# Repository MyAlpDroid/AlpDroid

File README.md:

<H1> Il existe désormais une version commerciale de la solution proposée et installée par les meilleurs préparateurs du marché </H1>

[Français](https://github.com/MyAlpDroid/AlpDroid/blob/main/README.md)    [English](https://github.com/MyAlpDroid/AlpDroid/blob/main/README.en.md)

Alpine : MyAlpdroid Video Demo 

<H1> Alpine : Remplacer le poste multimédia  par un poste Android </H1>

Le poste multimédia Alpine présente 2 inconvénients : il n'est pas compatible Android Auto/Apple CarPlay. Il a perdu au fur et à mesure les apps intéressantes comme Spotify via MySpin. On pourrait ajouter que l'écran 7 pouces peut sembler un peu petit.

Il présente aussi comme inconvénient qu'Alpine a manifestement décidé qu'il n'y aurait pas d'upgrade de celui-ci. Ceci étant d'autant plus dommage qu'il s'agit du même poste Multimédia **Bosch** que celui qu'on retrouve dans la Suzuki Swift 2014 et que l'écran **Valeo** est le même que celui du Renault Kadjar 2016.
Pour ces deux modèles, des upgrades ont été livrés pour faire bénéficier d'Android & Apple leurs utilisateurs. 
Bon, après, on parle de véhicules très haut de gamme (la swift et le Kadjar 2016), normal qu'il y ait un peu d'animation en après vente...

Bref, ce qu'on souhaite tout simplement c'est avoir ça :

Concernant l'Alpine, il est assez complexe de travailler sur une carte qui aurait pour objet d'intercepter le signal vidéo de l'Alpine pour permettre de switcher avec un adaptateur Android Auto ou CarPlay. Après avoir longuement étudié la question, la solution a semblé relativement couteuse et longue à produire. 

L'autre solution pourrait consister à adapter un poste Android avec l'écran de l'Alpine. On verra plus loin qu'il faudrait redévelopper une carte affichage et ajouter un contrôleur CAN pour réussir l'opération. C'est possible. Un peu complexe mais possible.

**La solution proposée ici** est donc d'intégrer un poste multimédia Android dernière génération à la place de l'ancien poste et de remplacer l'écran 7 pouces par l'écran de 8 à 11 pouces livré avec le poste Android.

Pour ma part, j'ai choisi ce poste de chez Joying :
[Joying Auto 10.1' Android 10](https://www.joyingauto.eu/joying-android-10-0-autoradio-10-1-inch-1280-800-screen-single-1din-car-stereo.html)

Tout l'enjeu est maintenant de faire fonctionner ce poste en lieu est place du "formidable" duo Valeo Bosch de l'Alpine A110.

Mais en premier, ce projet a pour objet de partager toute l'expérience et de permettre à ceux qui le souhaitent de faire la même chose et de contribuer à l'amélioration de la solution.

**Veuillez noter qu'il s'agit d'un projet expérimental, qu'il peut y avoir des dysfonctionnements dans les composants comme dans les programmes pouvant entrainer alarmes ou arrêt du véhicule pour mise en sécurité. Vous utilisez les résultats de ce projet à vos propres risques et périls, l'auteur n'assurera aucun support ou garantie suite à l'utilisation des programmes et informations issues de ce projet.**

Pour plus d'information, Consulter le Wiki :[ici](https://github.com/MyAlpDroid/AlpDroid/wiki)

Le projet s'inspire et utilise les résultats des projets suivants :

* Library Arduino et Serial USB : [ici](https://github.com/OmarAflak/Arduino-Library) qui s'appuie aussi sur Libray SerialUSB :[ici](https://github.com/felHR85/UsbSerial)
* Article et exemple de développement autour du CD4066 (multiplexeur à 2 voies) : J'ai perdu la référence, j'en suis désolé, je la remettrai si l'auteur se reconnait ou si je la retrouve entretemps.
* L'excellente Library CANBUS pour Arduino autowp : [ici](https://github.com/autowp/arduino-mcp2515)
* Exemple très bien documenté de pilotage d'une Mercedes et réingéniering des trames CAN : [ici](https://github.com/rnd-ash/W203-canbus)
* Library SpeedView pour les compteurs : [ici](https://github.com/anastr/SpeedView)
* Les services de reconnaissance de musique et service media de Scroball : [ici](https://github.com/peterjosling/scroball)
* Les API de l'application OsmAND pour le renvoi des directives de navigation vers le tableau de bord : [ici](https://github.com/osmandapp/osmand-api-demo)

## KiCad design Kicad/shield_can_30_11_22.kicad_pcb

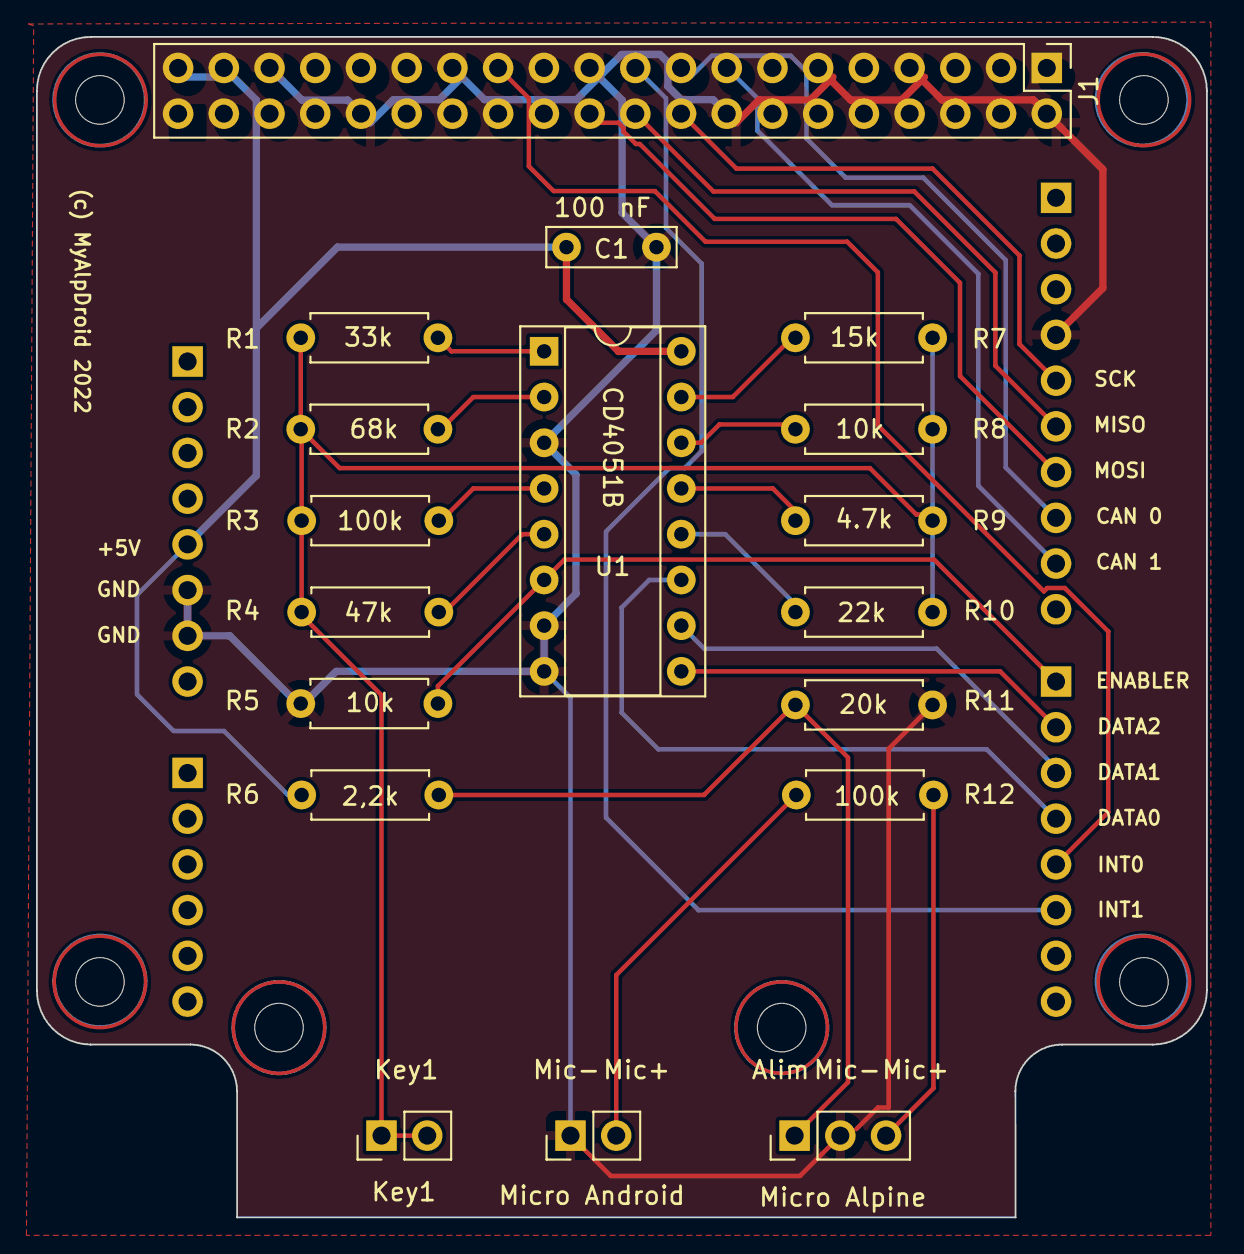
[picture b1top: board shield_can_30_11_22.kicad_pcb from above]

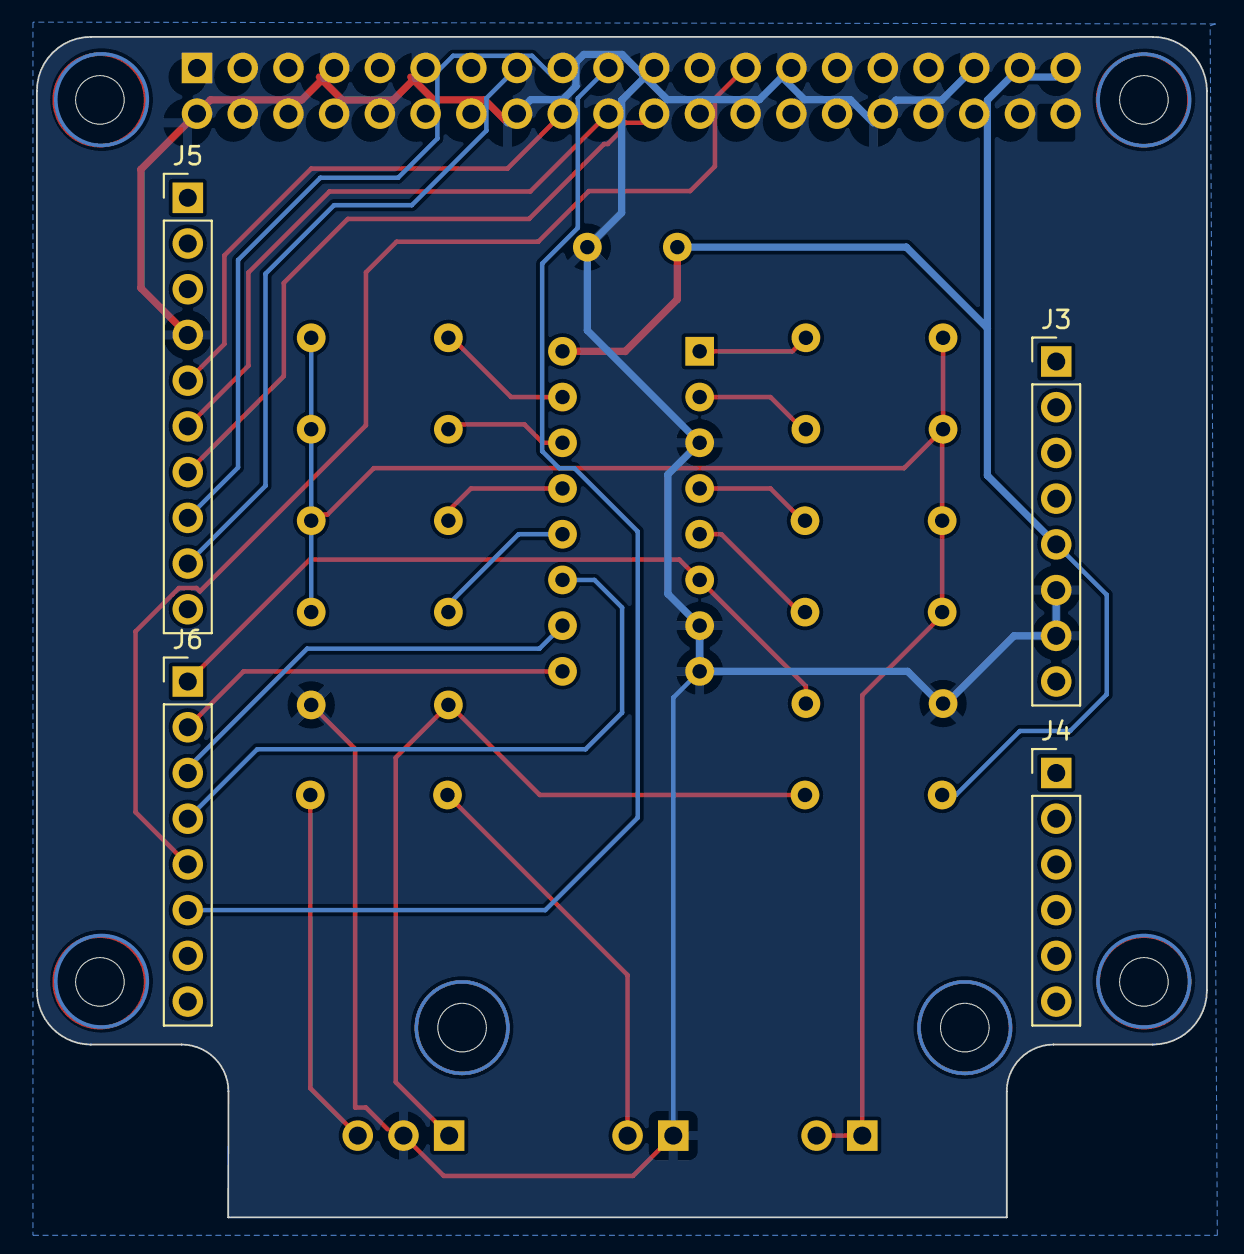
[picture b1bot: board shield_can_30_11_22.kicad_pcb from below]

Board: 2 copper layers, 65.0 x 65.6 mm, 28 parts (5 on the bottom side), 25 nets.

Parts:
C1: 100 nF; C_Rect_L7.0mm_W2.0mm_P5.00mm
J1: GPIO; PinHeader_2x20_P2.54mm_Vertical
J2: Micro Android; PinHeader_1x02_P2.54mm_Vertical
J3: Power; PinHeader_1x08_P2.54mm_Vertical
J4: Analog; PinHeader_1x06_P2.54mm_Vertical
J5: Digital/PWM; PinHeader_1x10_P2.54mm_Vertical
J6: Digital/PWM; PinHeader_1x08_P2.54mm_Vertical
J7: Key1; PinHeader_1x02_P2.54mm_Vertical
MH1, MH2, MH3, MH3#2, MH3#3, MH4: MountingHole_2.7mm_M2.5
Mic1: Micro Alpine; PinHeader_1x03_P2.54mm_Vertical
R1: 33k; R_Axial_DIN0207_L6.3mm_D2.5mm_P7.62mm_Horizontal
R2: 68k; R_Axial_DIN0207_L6.3mm_D2.5mm_P7.62mm_Horizontal
R3, R12: 100k; R_Axial_DIN0207_L6.3mm_D2.5mm_P7.62mm_Horizontal
R4: 47k; R_Axial_DIN0207_L6.3mm_D2.5mm_P7.62mm_Horizontal
R5, R8: 10k; R_Axial_DIN0207_L6.3mm_D2.5mm_P7.62mm_Horizontal
R6: 2,2K; R_Axial_DIN0207_L6.3mm_D2.5mm_P7.62mm_Horizontal
R7: 15k; R_Axial_DIN0207_L6.3mm_D2.5mm_P7.62mm_Horizontal
R9: 4.7k; R_Axial_DIN0207_L6.3mm_D2.5mm_P7.62mm_Horizontal
R10: 22k; R_Axial_DIN0207_L6.3mm_D2.5mm_P7.62mm_Horizontal
R11: 20K; R_Axial_DIN0207_L6.3mm_D2.5mm_P7.62mm_Horizontal
U1: CD4051B; DIP-16_W7.62mm_Socket

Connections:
+5V: C1.1, J1.2, J1.4, R6.1, U1.16 (VDD)
/4 (Data 0): J6.4, U1.11 (A)
/5 (Data 1): J6.3, U1.10 (B)
/6 (Data 2): J6.2, U1.9 (C)
/7: J6.1, R5.2, U1.6 (INH)
/9(CS CAN 1): J1.26, J5.9
/10(CS CAN 0): J1.24, J5.8
/11(MOSI): J1.19, J5.7
/12(MISO): J1.21, J5.6
/13(SCK): J1.23, J5.5
/GPIO[23]: J1.16, J6.5
/GPIO[25]: J1.22, J6.6
GND: C1.2, J1.6, J1.9, J1.14, J1.20, J1.25, J1.30, J1.34, J1.39, J2.1, J5.4, Mic1.2, R5.1, R11.1, U1.3 (X), U1.7 (VEE), U1.8 (VSS)
unnamed: J2.2, R12.2
unnamed: J7.1, J7.2, R1.2, R2.2, R3.2, R4.2, R7.2, R8.2, R9.2, R10.2
unnamed: Mic1.1, R6.2, R11.2
unnamed: Mic1.3, R12.1
unnamed: R1.1, U1.1 (X4)
unnamed: R2.1, U1.2 (X6)
unnamed: R3.1, U1.4 (X7)
unnamed: R4.1, U1.5 (X5)
unnamed: R7.1, U1.15 (X2)
unnamed: R8.1, U1.14 (X1)
unnamed: R9.1, U1.13 (X0)
unnamed: R10.1, U1.12 (X3)

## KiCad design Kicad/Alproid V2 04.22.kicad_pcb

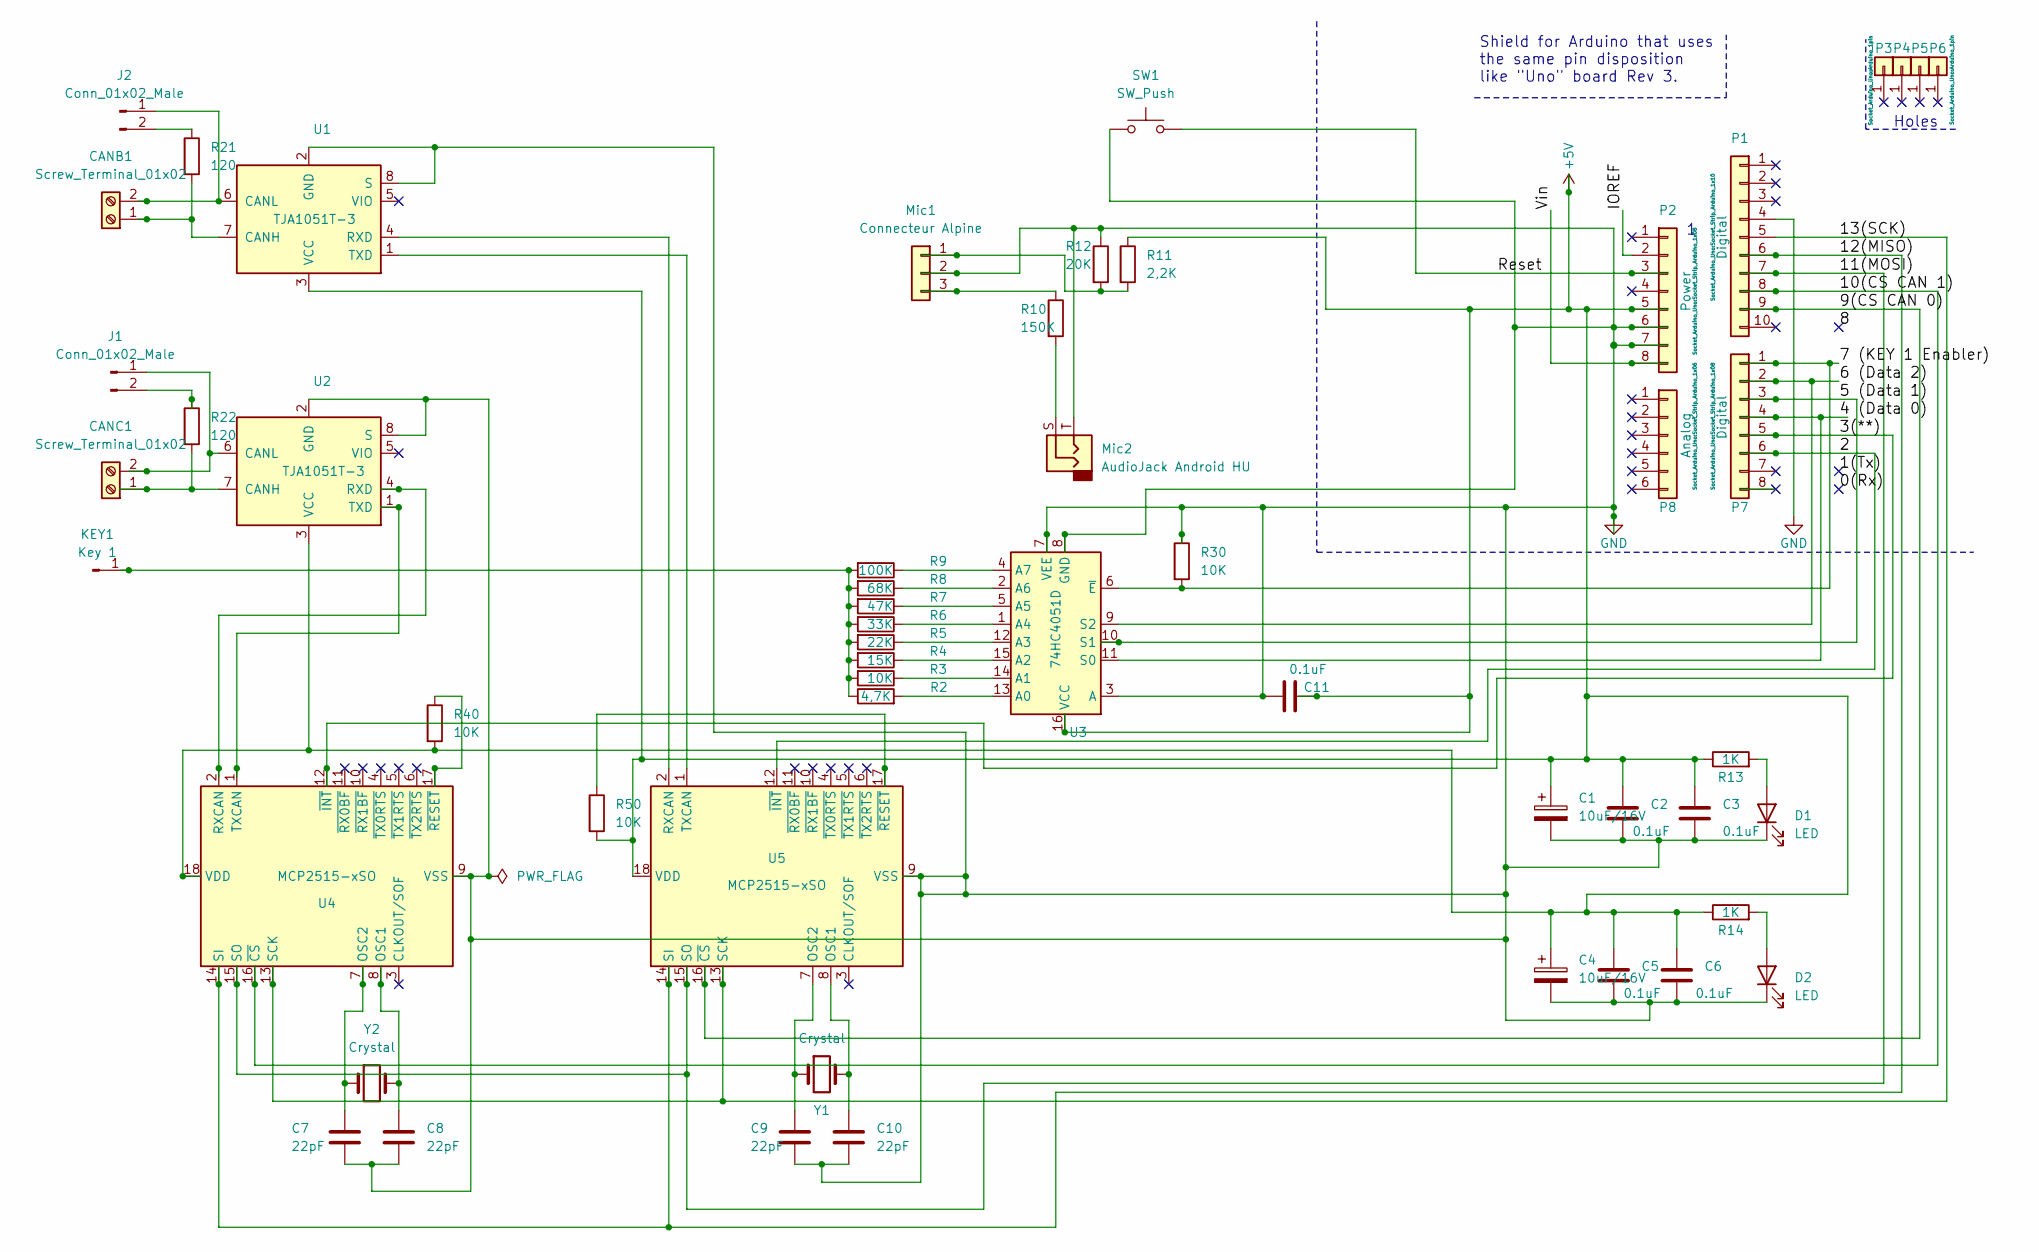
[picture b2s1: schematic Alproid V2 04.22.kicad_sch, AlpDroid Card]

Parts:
C1, C4: 10uF/16V; CP_Elec_3x5.3
C2, C3, C5, C6, C11: 0.1uF; C_1825_4564Metric
C7, C8, C9, C10: 22pF; C_1825_4564Metric
CANB1: Screw_Terminal_01x02; Altech_AK300_1x02_P5.00mm_45-Degree
CANC1: Screw_Terminal_01x02; Altech_AK300_1x02_P5.00mm_45-Degree
D1, D2: LED; LED_2010_5025Metric
J1, J2: Conn_01x02_Male; SolderJumper-2_P1.3mm_Bridged2Bar_Pad1.0x1.5mm
KEY1: Key 1; PinHeader_1x01_P1.00mm_Vertical
Mic1: Connecteur Alpine; Molex_Panelmate_53780-0570_1x05-1MP_P1.25mm_Horizontal
Mic2: AudioJack Android HU; Jack_3.5mm_CUI_SJ-3523-SMT_Horizontal
P1: Digital; Socket_Strip_Arduino_1x10
P2: Power; Socket_Strip_Arduino_1x08
P3, P4, P5, P6: CONN_01X01; Arduino_1pin
P7: Digital; Socket_Strip_Arduino_1x08
P8: Analog; Socket_Strip_Arduino_1x06
R2: 4,7K; R_2010_5025Metric
R3, R30, R40, R50: 10K; R_2010_5025Metric
R4: 15K; R_2010_5025Metric
R5: 22K; R_2010_5025Metric
R6: 33K; R_2010_5025Metric
R7: 47K; R_2010_5025Metric
R8: 68K; R_2010_5025Metric
R9: 100K; R_2010_5025Metric
R10: 150K; R_2010_5025Metric
R11: 2,2K; R_2010_5025Metric
R12: 20K; R_2010_5025Metric
R13, R14: 1K; R_2010_5025Metric
R21, R22: 120; R_2010_5025Metric
SW1: SW_Push; Panasonic_EVQPUJ_EVQPUA
U1, U2: TJA1051T-3; SOIC-8_3.9x4.9mm_P1.27mm
U3: 74HC4051D; SOIC-16_3.9x9.9mm_P1.27mm
U4, U5: MCP2515-xSO; SOIC-18W_7.5x11.6mm_P1.27mm
Y1, Y2: Crystal; Crystal_SMD_0603-2Pin_6.0x3.5mm

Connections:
+5V: C1.1, C2.1, C3.1, C4.1, C5.1, C6.1, C11.2, P2.5, R11.1, R13.1, R14.1, R40.2, R50.2, U1.3 (VCC), U2.3 (VCC), U3.16 (VCC), U4.18 (VDD), U5.18 (VDD)
/2: P7.6, U5.12 (~INT)
/3(**): P7.5, U4.12 (~INT)
/4 (Data 0): P7.4, U3.11 (S0)
/5 (Data 1): P7.3, U3.10 (S1)
/6 (Data 2): P7.2, U3.9 (S2)
/7 (KEY 1 Enabler): P7.1, R30.2, U3.6 (~E)
/9(CS CAN 0): P1.9, U5.16 (~CS)
/10(CS CAN 1): P1.8, U4.16 (~CS)
/11(MOSI): P1.7, U4.15 (SO), U5.15 (SO)
/12(MISO): P1.6, U4.14 (SI), U5.14 (SI)
/13(SCK): P1.5, U4.13 (SCK), U5.13 (SCK)
/IOREF: P2.2
/Reset: P2.3, SW1.2
/Vin: P2.8
GND: C1.2, C2.2, C3.2, C4.2, C5.2, C6.2, C7.2, C8.2, C9.2, C10.2, C11.1, D1.1 (K), D2.1 (K), Mic1.2, Mic2.T, P1.4, P2.6, P2.7, R12.1, R30.1, SW1.1, U1.2 (GND), U1.8 (S), U2.2 (GND), U2.8 (S), U3.3 (A), U3.7 (VEE), U3.8 (GND), U4.9 (VSS), U5.9 (VSS)
unnamed: C7.1, U4.7 (OSC2), Y2.1
unnamed: C8.1, U4.8 (OSC1), Y2.2
unnamed: C9.1, U5.7 (OSC2), Y1.1
unnamed: C10.1, U5.8 (OSC1), Y1.2
unnamed: CANB1.1, R21.2, U1.7 (CANH)
unnamed: CANB1.2, J2.1, U1.6 (CANL)
unnamed: CANC1.1, R22.2, U2.7 (CANH)
unnamed: CANC1.2, J1.1, U2.6 (CANL)
unnamed: D1.2 (A), R13.2
unnamed: D2.2 (A), R14.2
unnamed: J1.2, R22.1
unnamed: J2.2, R21.1
unnamed: KEY1.1, R2.1, R3.2, R4.2, R5.2, R6.2, R7.2, R8.2, R9.2
unnamed: Mic1.1, R11.2, R12.2
unnamed: Mic1.3, R10.1
unnamed: Mic2.S, R10.2
unnamed: R2.2, U3.13 (A0)
unnamed: R3.1, U3.14 (A1)
unnamed: R4.1, U3.15 (A2)
unnamed: R5.1, U3.12 (A3)
unnamed: R6.1, U3.1 (A4)
unnamed: R7.1, U3.5 (A5)
unnamed: R8.1, U3.2 (A6)
unnamed: R9.1, U3.4 (A7)
unnamed: R40.1, U4.17 (~RESET)
unnamed: R50.1, U5.17 (~RESET)
unnamed: U1.1 (TXD), U5.1 (TXCAN)
unnamed: U1.4 (RXD), U5.2 (RXCAN)
unnamed: U2.1 (TXD), U4.1 (TXCAN)
unnamed: U2.4 (RXD), U4.2 (RXCAN)

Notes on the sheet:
Holes
Shield for Arduino that uses the same pin disposition like "Uno" board Rev 3.

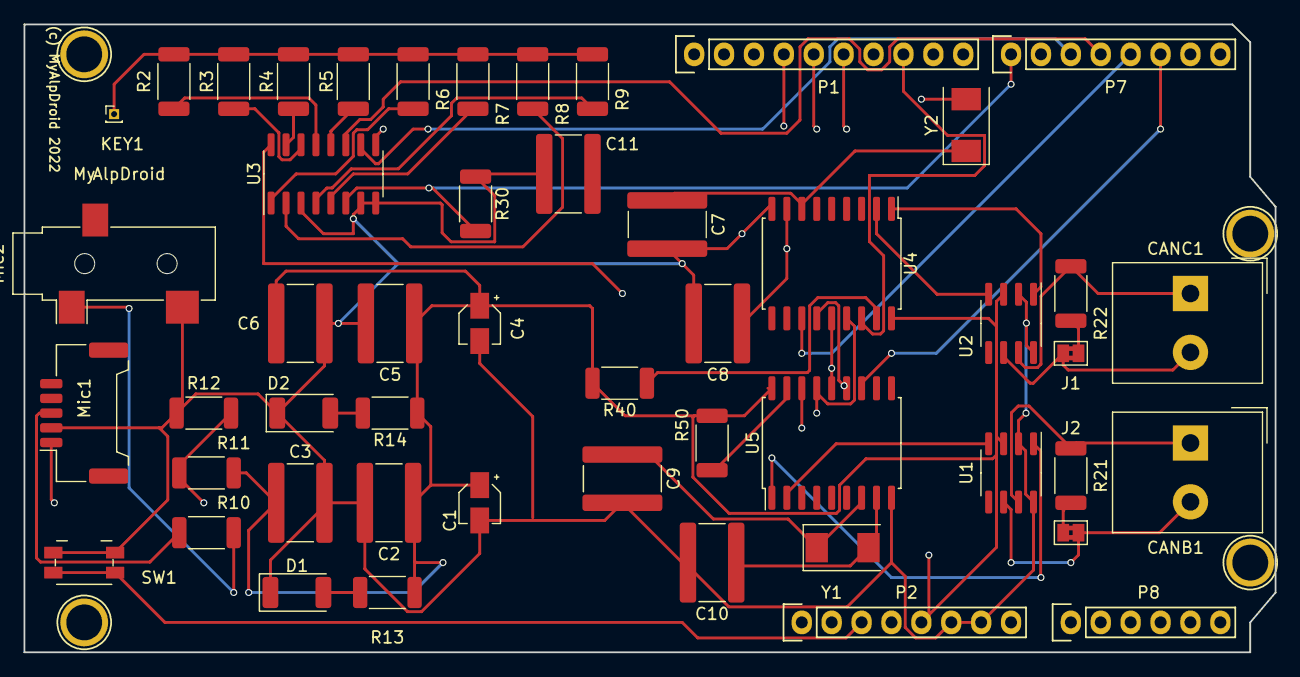
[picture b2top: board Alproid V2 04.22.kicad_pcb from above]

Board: 4 copper layers, 106.3 x 53.3 mm, 54 parts (0 on the bottom side), 44 nets.

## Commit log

2022-07-15 First upload
2022-07-16 Second upload
2022-07-16 Create LICENSE
2022-07-16 Update issue templates
2022-11-16 Update UNO CODE better frame control
    Option for new 2 Channel Can Bus - @Dav42 new pcb card
2022-11-16 Kit simplifié par Dav42
2023-01-18 Add files via upload
    Tuto de montage
2023-01-22 Create Boitier 3D
2023-01-22 3D printing sketch
2023-02-08 add screen support 3D printed
2023-05-14 Merge remote-tracking branch 'remote/main'
    Autofolding & cold country handbrake (not tested)
2023-05-20 Merge remote-tracking branch 'remote/main'
    Code cleaning
2023-05-21 Merge remote-tracking branch 'remote/main'
    Code cleaning /2
2023-05-31 Merge remote-tracking branch 'remote/main'
    Code cleaning /3
2023-06-18 Merge remote-tracking branch 'remote/main'
    Code cleaning /4 - Switch Active (except speed signal)
2023-07-14 Merge remote-tracking branch 'remote/main'
    Change needle / Compass / Start&Stop
2023-08-05 Merge remote-tracking branch 'remote/main'
    OsmAnd Builder update
2023-08-13 Merge remote-tracking branch 'remote/main'
    adding roadbook / new obd command
2023-08-17 Merge remote-tracking branch 'remote/main'
    track data / obd control / roadbook update
2023-09-03 Merge remote-tracking branch 'remote/main'
    bargraphes
2023-09-03 Merge remote-tracking branch 'remote/main'
    bargraphes 3.3.0
2023-09-06 Merge remote-tracking branch 'remote/main'
    addon to Tripmaster
2023-09-10 Merge remote-tracking branch 'remote/main'
    bugs+Fuel Temperature+Hp
2023-10-13 Merge remote-tracking branch 'remote/main'
    review
2023-10-19 Merge remote-tracking branch 'remote/main'
    new engine & confort screens
2023-10-29 Merge remote-tracking branch 'remote/main'
    redesign counters & media buttons
2023-11-01 Merge remote-tracking branch 'remote/main'
    Tuto rev 1
2024-02-04 Merge remote-tracking branch 'remote/main'
    update img
